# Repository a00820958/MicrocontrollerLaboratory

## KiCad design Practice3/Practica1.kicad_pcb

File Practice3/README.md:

# Practice 3. Developiong the PCB (Fabrication)

## Objectives

Build the minimum system from the designs that thei student made on the practices 1 and 2.

## Introduction

Microcontrollers are all around  he world. Each day, Microcontrollers, are more present in the many aspects of our lives: in our work, inside our houses, and in more. We can find them controlling small devices like cellphones, microwaves, washing machines, and televisions.

A microcontroller is one device or chip that is used to govern one or more processes. For example, the controller that regulates the room temperature of an air conditioner; it has a sensor that continuously measures the internal temperature and, when the preset limits are exceeded, it generates the necessary signals to adjust the temperature.

## State of the Art

### The practices and the PIC microcontroller

The main objective of this practices is to provide students the foundation to fully understand the operation of the PIC18F45K50 microcontroller. This will be achieved through 11 documents that will guide the reader to create their own electronic card or Printed Circuit Board (PCB) and to be able to program it; in order to, execute different functions.

The advantages of ta PIC microcontroller to others on the market, which is why it will be used throughout this manual, are as follows:

- Easy to operate.
- There is enough documentation to work with it and it’s easy to obtain it.
- The price is comparatively lower than its competitors.
- It has a high operating speed.
- Development tools are cheap and easy to use.
- There are a variety of hardware that can record, erase and check the behavior of PIC.
- Once you learn to handle a PIC, it will easier to handle any other models of microcontrollers.

### KiCad EDA Software

KiCad is an open source software suite for Electronic Design Automation (EDA). The programs handle Schematic Capture,
and PCB Layout with Gerber output. The suite runs on Windows, Linux and macOS and is licensed under GNU GPL v3. The
first release date was in 1992 by its original author, Jean-Pierre Charras, but is now currently under development by
the KiCad Developers Team. 

## Results

In this section, you must report the outcomes of the laboratory activities.

### Follow the next 'Project Configuration' Steps

1. Now that your PCB is completed, you can generate the Gerber files for each layer of your board. Click on Perform design rules check as shown in Fig. 1. Then click on the Run DCR, if everything goes right you will get no message of error, as show in figure 2.

2. Click on File→Plot... Select ‘Gerber’ as ‘Plot Format,’also you must choose a folder to save your generated files. Make sure that only the next options are selected: B.Cu from ‘Layers’ box, Exclude PCB edge layer from other layers from ‘Options’ box, and Use proper filename extensions from ‘Gerber Options’ box; as shown in Fig. 3.

3. Finally, click on ‘Plot’ and then click on Generate Drill File. A new window will appear with some options on default. In the section Excellon Drill File Options select the ‘PTH and NPTH holes in single file’ box, then click on the button ‘Generate Drill File.’ Next, in the section Drill Map File Format change to ‘PDF’ box and click on ‘Generate Drill File’ again, see Fig. 4.

4. Once the Gerber and Drill files are generated, you can check your track design [here](https://www.pcbgogo.com/GerberViewer.html). Use the file with the .gbl and .drl extension.

### Report
For this practice, modify only the Conclusion section. Commit an push the changes on the fork of this repository and add
upload the link on Canvas.

### File uploads
Commit and push the files with extensions .pro, .gbl, and .drl  created once you completed all the steps of the document in the repository.

### Demonstration
Screenshot the image of the complete PBC board whith the attached electronic components using the 3d viewer of KiCad.

## Conclusion

I tried doing this practice but I had so many errors I did not know how to fix. I think that during class we should try to address the problems we are having in kicad and how to fix them because I couldn't do this part very well because of the errors I had before and didn't know how to fix. Overall, kidcad is relatively easy to use except when there are errors we don't understand.

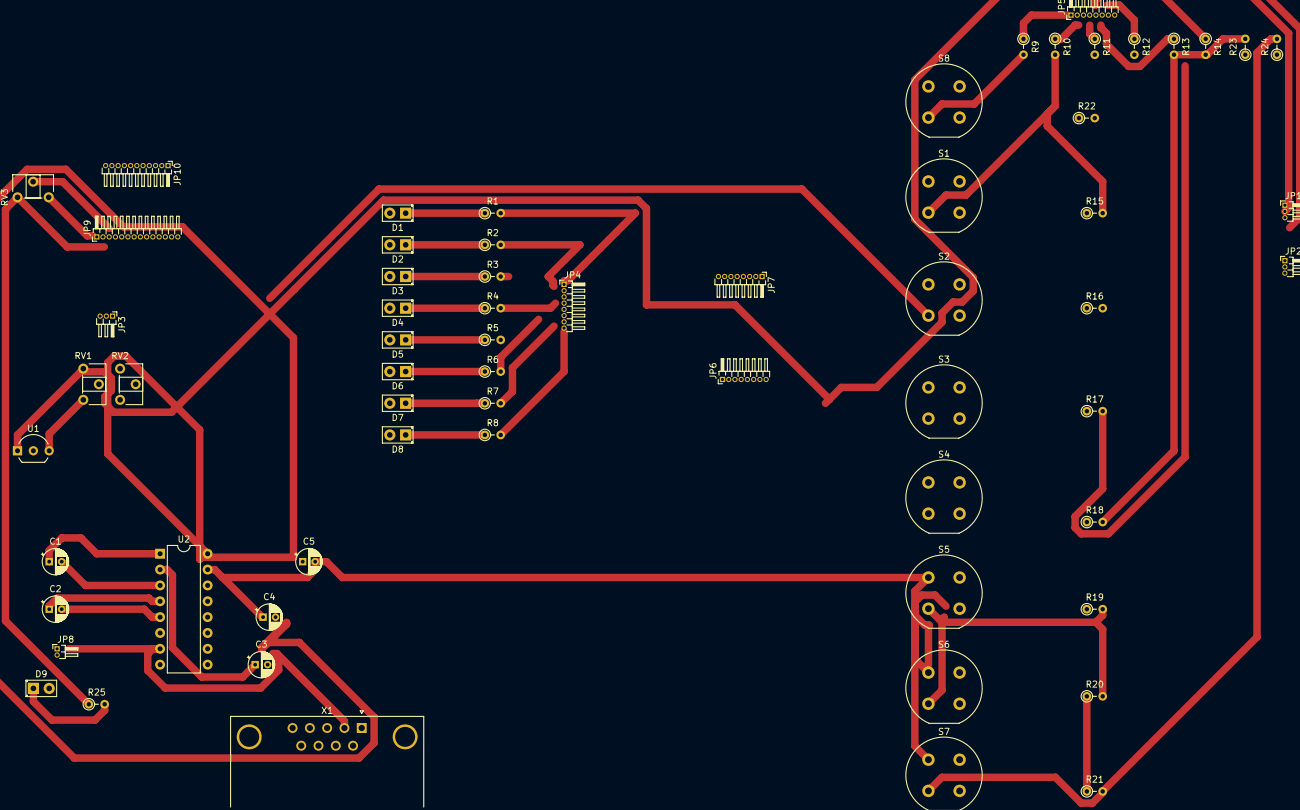
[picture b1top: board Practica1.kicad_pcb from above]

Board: 2 copper layers, 63 parts (0 on the bottom side), 68 nets.

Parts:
C1, C2, C3, C4, C5: CP; CP_Radial_D4.0mm_P2.00mm
D1, D2, D3, D4, D5, D6, D7, D8, D9: LED; LED_D2.0mm_W4.8mm_H2.5mm_FlatTop
JP1, JP2, JP3: PINHD-1X3; PinHeader_1x03_P1.00mm_Horizontal
JP4, JP5, JP6, JP7: PINHD-1X8; PinHeader_1x08_P1.00mm_Horizontal
JP8: PINHD-1X2; PinHeader_1x02_P1.00mm_Horizontal
JP9: PINHD-1X14; PinHeader_1x14_P1.00mm_Horizontal
JP10: PINHD-1X11; PinHeader_1x11_P1.00mm_Horizontal
R1, R2, R3, R4, R5, R6, R7, R8, R25: 470; R_Axial_DIN0204_L3.6mm_D1.6mm_P2.54mm_Vertical
R9, R10, R11, R12, R13, R14, R23, R24: 1k; R_Axial_DIN0204_L3.6mm_D1.6mm_P2.54mm_Vertical
R15, R16, R17, R18, R19, R20, R21, R22: 4.7k; R_Axial_DIN0204_L3.6mm_D1.6mm_P2.54mm_Vertical
RV1, RV2, RV3: POT; Potentiometer_ACP_CA6-H2,5_Horizontal
S1, S2, S3, S4, S5, S6, S7, S8: DTS-6; Push_E-Switch_KS01Q01
U1: MCP9700A; TO-92_Inline_Wide
U2: MAX232; DIP-16_W7.62mm
X1: F09HP; DSUB-9_Female_Horizontal_P2.77x2.84mm_EdgePinOffset9.90mm_H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

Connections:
+5V: C3.2, C5.1, JP1.1, JP1.2, JP1.3, RV1.1, U1.1, U2.16
+5VA: JP9.2, R15.1, R16.1, R17.1, R18.1, R19.1, R20.1, R21.1, R22.1, R25.1, RV3.1
GNDA: C4.1, C5.2, JP9.1, RV1.3, RV2.1, RV3.3, S1.1, S2.1, S3.1, S4.1, S5.1, S6.1, S7.1, S8.1, U1.3, U2.15, X1.5
unnamed: C1.1, U2.1
unnamed: C1.2, U2.3
unnamed: C2.1, U2.4
unnamed: C2.2, U2.5
unnamed: C3.1, U2.2
unnamed: C4.2, U2.6
unnamed: D1.1, R1.1
unnamed: D1.2, D2.2, D3.2, D4.2, D5.2, D6.2, D7.2, D8.2
unnamed: D2.1, R2.1
unnamed: D3.1, R3.1
unnamed: D4.1, R4.1
unnamed: D5.1, R5.1
unnamed: D6.1, R6.1
unnamed: D7.1, R7.1
unnamed: D8.1, R8.1
unnamed: D9.1, R25.2
unnamed: D9.2, U2.9
unnamed: JP2.1, JP2.2, JP2.3
unnamed: JP3.1, RV2.2
unnamed: JP3.2, U1.2
unnamed: JP3.3, RV1.2
unnamed: JP4.1, R1.2
unnamed: JP4.2, R2.2
unnamed: JP4.3, R3.2
unnamed: JP4.4, R4.2
unnamed: JP4.5, R5.2
unnamed: JP4.6, R6.2
unnamed: JP4.7, R7.2
unnamed: JP4.8, R8.2
unnamed: JP5.1, R9.1
unnamed: JP5.2, R10.1
unnamed: JP5.3, R11.1
unnamed: JP5.4, R12.1
unnamed: JP5.5, R13.1
unnamed: JP5.6, R14.1
unnamed: JP5.7, R23.1
unnamed: JP5.8, R24.1
unnamed: JP6.1, JP7.1
unnamed: JP6.2, JP7.2
unnamed: JP6.3, JP7.3
unnamed: JP6.4, JP7.4
unnamed: JP6.5, JP7.5
unnamed: JP6.6, JP7.6
unnamed: JP6.7, JP7.7
unnamed: JP6.8, JP7.8
unnamed: JP9.3, RV3.2
unnamed: JP9.4, JP10.1
unnamed: JP9.5, JP10.2
unnamed: JP9.6, JP10.3
unnamed: JP9.7, JP10.4
unnamed: JP9.8, JP10.5
unnamed: JP9.9, JP10.6
unnamed: JP9.10, JP10.7
unnamed: JP9.11, JP10.8
unnamed: JP9.12, JP10.9
unnamed: JP9.13, JP10.10
unnamed: JP9.14, JP10.11
unnamed: R10.2, R15.2, S1.3
unnamed: R11.2, R16.2, S2.3
unnamed: R12.2, R17.2, S3.3
unnamed: R13.2, R14.2, R18.2, R19.2, R20.2, R23.2, S4.3, S5.3, S6.3
unnamed: R21.2, R24.2, S7.3
unnamed: R9.2, R22.2, S8.3
unnamed: U2.7, X1.2
unnamed: U2.8, X1.3

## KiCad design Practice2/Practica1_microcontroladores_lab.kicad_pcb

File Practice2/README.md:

# Practice 2. Developiong the PCB (Layout)

## Objectives

Develop the connection diagrams (layout) from the schematic diagram.

## Introduction

Microcontrollers are all around  he world. Each day, Microcontrollers, are more present in the many aspects of our lives: in our work, inside our houses, and in more. We can find them controlling small devices like cellphones, microwaves, washing machines, and televisions.

A microcontroller is one device or chip that is used to govern one or more processes. For example, the controller that regulates the room temperature of an air conditioner; it has a sensor that continuously measures the internal temperature and, when the preset limits are exceeded, it generates the necessary signals to adjust the temperature.

## State of the Art

### The practices and the PIC microcontroller

The main objective of this practices is to provide students the foundation to fully understand the operation of the PIC18F45K50 microcontroller. This will be achieved through 11 documents that will guide the reader to create their own electronic card or Printed Circuit Board (PCB) and to be able to program it; in order to, execute different functions.

The advantages of ta PIC microcontroller to others on the market, which is why it will be used throughout this manual, are as follows:

- Easy to operate.
- There is enough documentation to work with it and it’s easy to obtain it.
- The price is comparatively lower than its competitors.
- It has a high operating speed.
- Development tools are cheap and easy to use.
- There are a variety of hardware that can record, erase and check the behavior of PIC.
- Once you learn to handle a PIC, it will easier to handle any other models of microcontrollers.

### KiCad EDA Software

KiCad is an open source software suite for Electronic Design Automation (EDA). The programs handle Schematic Capture,
and PCB Layout with Gerber output. The suite runs on Windows, Linux and macOS and is licensed under GNU GPL v3. The
first release date was in 1992 by its original author, Jean-Pierre Charras, but is now currently under development by
the KiCad Developers Team. 

## Results

In this section, you must report the outcomes of the laboratory activities.

### Follow the next 'Project Configuration' Steps

1. In  the  same  project  from  practice  1,  click  on  the  icon ‘Assign PCB footprints to schematic symbols’.  By  doing  so,  you  will  be  able  to  watch  the  footprints associations in a list format. ***NOTE:*** *If a ***‘Confirmation’*** window pops to reassign all the components to a new library format, click ‘No.’*

2. Now it is time to add the corresponding libraries to the Cvpcbprogram.   Download from [here](./modules)  the modules   needed   for   the   project.   Click   on Preferences→Manage Footprint Libraries...and  in this  way  you  will  be  able  to  add  the  modules  from the folder  named  ‘modules.’  Click  on  ‘Project  Specific Libraries...’  tab,  then  click  on  the  button  ‘Browse Libraries...’ and search for the folder  where  you  save the modules. Select all the files and click ‘OK.’Fig.  1 shows the result of the added modules. NOTE:Your KiCad EDA Software must be in english to add the modules.

3. Once  that  is  done,  you  must  associate  the  list  of components  with  its  respective  footprint using Table  I for  guidance.  Be  sure  to  activate  the  option  ‘Filter footprints  list  by  library’ from  the Cvpcbtoolbar. To associate  the  components  showed  in  the middle  column,  double  click  with  their  corresponding footprint from the right column. ***NOTE:*** *Search  all  the  footprints  in  the*  ***‘user’*** *and * 
***‘discrete’*** * added libraries that should be found at the end of the list.*

4. Save   your modifications  by  clicking  **‘Apply,  Save Schematic & Continue,’ and then click ‘OK.’**
5. After that, you may close the Cvpcband go back to the EESchema (Schematic  Editor.)  Save  your  project  by clicking   on File→Save.   Close   the   editor   of   the Schematic and switch back to the **‘Project Manager.’**

6. Once you have the design of the circuit on the schematic, it is time to generate the **‘layout’** of our PCB  using the Netlist  file. On  the Project  Manager program  from KiCad, click on the icon **‘PCB layout editor’** . A new window will appear from the PCBNew. Click **‘Yes’** in the confirmation window.
7. On  the  toolbar  menu  from  the PCBNew click  on  the **‘Page  Settings  for  paper  size  and  texts’**
and modify the size settings to **‘USLetter 8.5x11in.’**

8. After  that,  it  will be  time  to  focus  more  on  design concepts.  You  may  do  so  by  opening  the
menu  of **‘Setup→Design Rules...’**. On   it,   some   final   design characteristics will appear with many millimeter values. Between   them,   you   should   find  the  **‘Clearance’** specification  which  is  the  smallest  spaces  that  it  must exist  between  the tracks  on the  PCB.  You  shall  set the value of this cell to 0.508 mm (0.020 inches.) Next, we set  a  value  of 1.200  mm  (0.047244 inches)on the  cell of **‘Track Width.’** 

9. Switch now to the ‘Global Design Rules’ tab and write, if needed, the minimum values for each an every one of the parameters on the ‘Minimum Allowed Values’ box. Click ‘OK.’

10. Time  to  import  the  Netlist  file.  Go  to  the  toolbar ‘Tools→Update  PCB  from  Schematic...’  and  then click on ‘Update  PCB.’ When  you  close  the  window all the components will appear on the screen.

11.Check in the ‘Layers Manager’ window (located at the right  part  of  your  screen) that all  the needed  boxes  are
checked, as shown:

11.Check in the ‘Layers Manager’ window (located at the right  part  of  your  screen) that all  the needed  boxes  are checke

12. Now you  have  to  define  the  limits  of  the  PCB.  First, highlight  the  ‘Edge.Cuts’  layer.  Then,  select  the  ‘Add  graphic lines’ tool and began to trace the original measures of your copper board (15x20 cm.) You must also define the  cutting  area;  do  not  forget  to  add  a  2.5  cm  margin around the board. To measure the lines, you can use the ‘Add dimension’ tool located on the right.

13. It is your turn to move all the components in the circuit in  order  to  avoid  any  track  intersection  inside  the working   area.   You   can   move   the   components   by positioning your mouse pointer above it and pressing the key [G]. All the components are connected to each other by a group of wires called ratsnest. Make sure that the icon  of  **‘Hide  board  ratsnest’** located  in  the toolbar of the left is highlighted.

14. Now you must link all the connections of you PCB. But before  that,  you  must  change  the  drawing  option  from the right toolbar from ‘Edge.Cuts’ to ‘B.Cu (PgDn)’ (B->Bottom, Cu->Copper.).

15. Start to connect your tracks to each and every one pin on the schematic by using the icon ‘Route Tracks’. Trace  all  the  routes  for  each  net  or  connection  in  your PCB design.

16. Once  your  are  done,  save  your  layout  File->Save  or using the command [Ctrl + S].

17. Your board must look like:

### Report
For this practice, modify only the Conclusion section. Commit an push the changes on the fork of this repository and add
upload the link on Canvas.

### File uploads
Commit and push the files with extensions .pro and .kicad_pcb created once you completed all the steps of the document in the repository.

### Demonstration
Screenshot the image of the complete schematic and upload it at the repository.

## Conclusion

This practice was much harder than the last one because we had to do more things that were very new. I wish I had understood some this better becasue I could not make this practice work. I think that I got very confused in the instructions even though they were very clear. I think we need a little more practice with kicad becasue last practice was much easier to complete. I hope that the next practice goes better than this one.

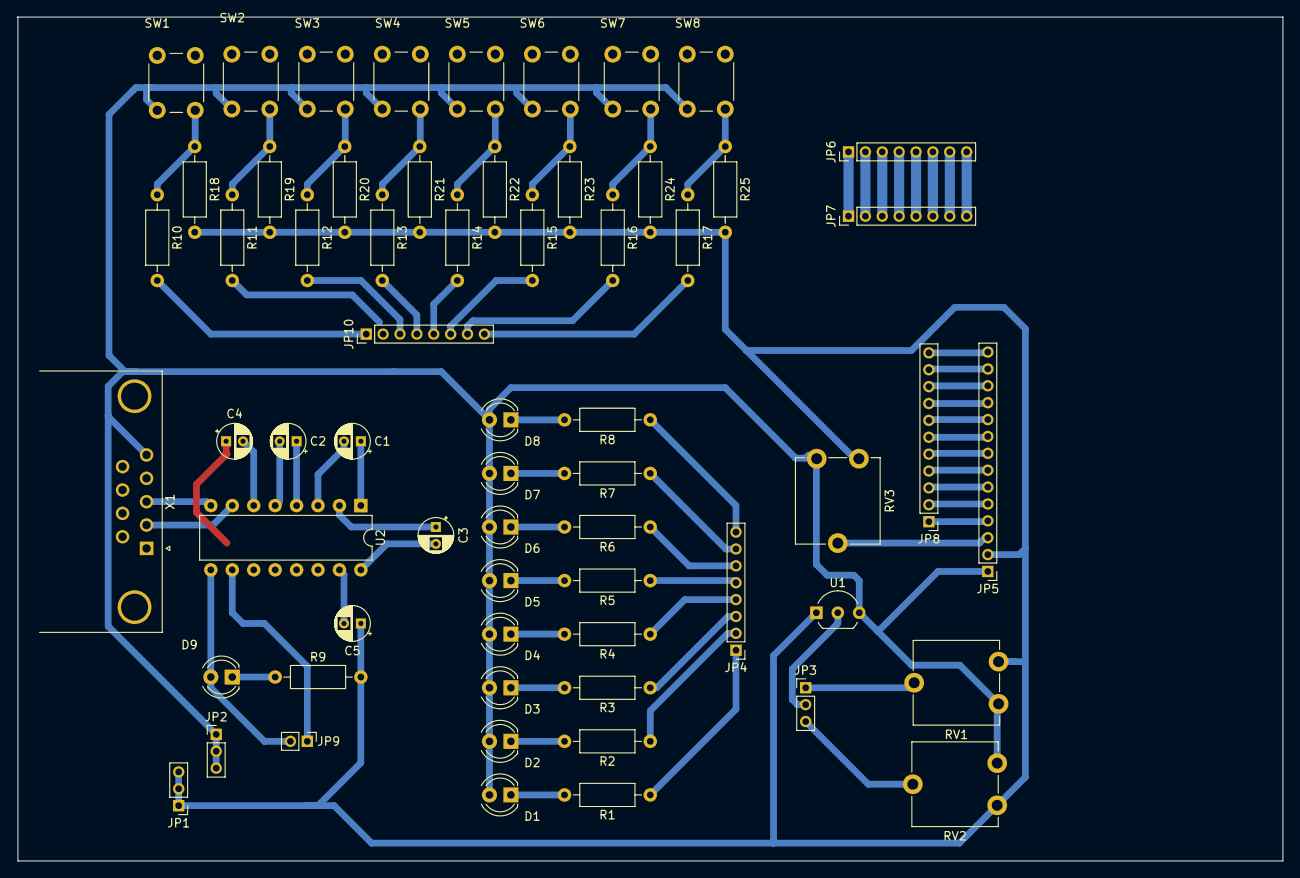
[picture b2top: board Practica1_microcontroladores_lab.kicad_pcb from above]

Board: 2 copper layers, 150.0 x 100.0 mm, 63 parts (0 on the bottom side), 69 nets.

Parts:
C1, C2, C3, C4, C5: 10u; CP_Radial_D4.0mm_P2.00mm
D1, D2, D3, D4, D5, D6, D7, D8, D9: LED; LED_D4.0mm
JP1, JP2, JP3: PINHD-1X3; PinHeader_1x03_P2.00mm_Vertical
JP4, JP6, JP7, JP10: PINHD-1X8; PinHeader_1x08_P2.00mm_Vertical
JP5: PINHD-1X14; PinHeader_1x14_P2.00mm_Vertical
JP8: PINHD-1X11; PinHeader_1x11_P2.00mm_Vertical
JP9: PINHD-1X2; PinHeader_1x02_P2.00mm_Vertical
R1, R2, R3, R4, R5, R6, R7, R8, R9: 470; R_Axial_DIN0207_L6.3mm_D2.5mm_P10.16mm_Horizontal
R10, R11, R12, R13, R14, R15, R16, R17: 1K; R_Axial_DIN0207_L6.3mm_D2.5mm_P10.16mm_Horizontal
R18, R19, R20, R21, R22, R23, R24, R25: 4.7K; R_Axial_DIN0207_L6.3mm_D2.5mm_P10.16mm_Horizontal
RV1, RV2, RV3: 10K; Potentiometer_ACP_CA9-V10_Vertical
SW1, SW2, SW3, SW4, SW5, SW6, SW7, SW8: SW_PUSH; SW_PUSH_6mm
U1: MCP9700A; TO-92_Inline_Wide
U2: MAX232; DIP-16_W7.62mm
X1: F09HP; DSUB-9_Female_Horizontal_P2.77x2.84mm_EdgePinOffset9.90mm_H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

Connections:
+5V: C3.2, C5.1, JP1.1, JP1.2, JP1.3, JP5.2, R9.2, R18.2, R19.2, R20.2, R21.2, R22.2, R23.2, R24.2, R25.2, RV1.1, RV2.3, RV3.3, U1.1, U2.16
GND: D1.2, D2.2, D3.2, D4.2, D5.2, D6.2, D7.2, D8.2, JP2.1, JP2.2, JP2.3, JP5.1, RV1.3, RV2.1, RV3.1, SW1.1, SW2.1, SW3.1, SW4.1, SW5.1, SW6.1, SW7.1, SW8.1, U1.3, X1.5
unnamed: C1.1, U2.1
unnamed: C1.2, U2.3
unnamed: C2.1, U2.4
unnamed: C2.2, U2.5
unnamed: C3.1, U2.2
unnamed: C4.1, C5.2, U2.15
unnamed: C4.2, U2.6
unnamed: D1.1, R1.2
unnamed: D2.1, R2.2
unnamed: D3.1, R3.2
unnamed: D4.1, R4.2
unnamed: D5.1, R5.2
unnamed: D6.1, R6.2
unnamed: D7.1, R7.2
unnamed: D8.1, R8.2
unnamed: D9.1, R9.1
unnamed: D9.2, JP9.2, U2.9
unnamed: JP3.1, RV1.2
unnamed: JP3.2, U1.2
unnamed: JP3.3, RV2.2
unnamed: JP4.1, R1.1
unnamed: JP4.2, R2.1
unnamed: JP4.3, R3.1
unnamed: JP4.4, R4.1
unnamed: JP4.5, R5.1
unnamed: JP4.6, R6.1
unnamed: JP4.7, R7.1
unnamed: JP4.8, R8.1
unnamed: JP5.3, RV3.2
unnamed: JP5.4, JP8.1
unnamed: JP5.5, JP8.2
unnamed: JP5.6, JP8.3
unnamed: JP5.7, JP8.4
unnamed: JP5.8, JP8.5
unnamed: JP5.9, JP8.6
unnamed: JP5.10, JP8.7
unnamed: JP5.11, JP8.8
unnamed: JP5.12, JP8.9
unnamed: JP5.13, JP8.10
unnamed: JP5.14, JP8.11
unnamed: JP6.1, JP7.1
unnamed: JP6.2, JP7.2
unnamed: JP6.3, JP7.3
unnamed: JP6.4, JP7.4
unnamed: JP6.5, JP7.5
unnamed: JP6.6, JP7.6
unnamed: JP6.7, JP7.7
unnamed: JP6.8, JP7.8
unnamed: JP9.1, U2.10
unnamed: JP10.1, R10.2
unnamed: JP10.2, R11.2
unnamed: JP10.3, R12.2
unnamed: JP10.4, R13.2
unnamed: JP10.5, R14.2
unnamed: JP10.6, R15.2
unnamed: JP10.7, R16.2
unnamed: JP10.8, R17.2
unnamed: R10.1, R18.1, SW1.2
unnamed: R11.1, R19.1, SW2.2
unnamed: R12.1, R20.1, SW3.2
unnamed: R13.1, R21.1, SW4.2
unnamed: R14.1, R22.1, SW5.2
unnamed: R15.1, R23.1, SW6.2
unnamed: R16.1, R24.1, SW7.2
unnamed: R17.1, R25.1, SW8.2
unnamed: U2.7, X1.2
unnamed: U2.8, X1.3
